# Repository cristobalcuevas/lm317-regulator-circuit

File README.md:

# LM317 Regulator Circuit

## PCB Design

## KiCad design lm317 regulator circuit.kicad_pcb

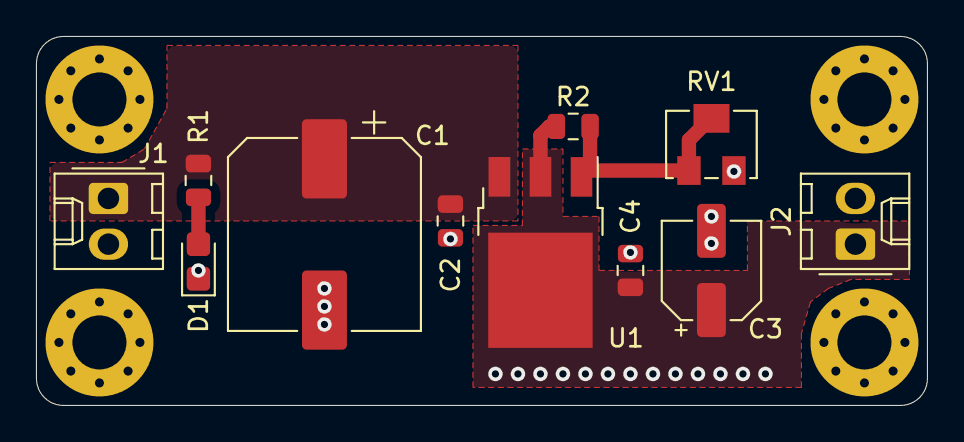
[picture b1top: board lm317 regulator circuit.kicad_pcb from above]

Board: 2 copper layers, 49.5 x 20.5 mm, 15 parts (0 on the bottom side), 5 nets.

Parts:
C1: 1000uF/25V; CP_Elec_10x12.5
C2, C4: 0.1uF/50V; C_0805_2012Metric
C3: 100uF/25V; CP_Elec_5x5.4
D1: LED; LED_0805_2012Metric_Castellated
H1, H2, H3, H4: MountingHole; MountingHole_3mm_Pad_Via
J1: INPUT; Molex_KK-254_AE-6410-02A_1x02_P2.54mm_Vertical
J2: OUTPUT; Molex_KK-254_AE-6410-02A_1x02_P2.54mm_Vertical
R1: 2.2k; R_0805_2012Metric
R2: 220; R_0805_2012Metric
RV1: 1k; Potentiometer_Bourns_3224W_Vertical
U1: LM317L_TO92; TO-252-3_TabPin2

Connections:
GND: C1.2, C2.2, C3.2, C4.2, D1.1, J1.2, J2.2, RV1.3
unnamed: C1.1, C2.1, J1.1, R1.1, U1.3
unnamed: C3.1, C4.1, J2.1, R2.1, U1.2
unnamed: D1.2, R1.2
unnamed: R2.2, RV1.1, RV1.2, U1.1
